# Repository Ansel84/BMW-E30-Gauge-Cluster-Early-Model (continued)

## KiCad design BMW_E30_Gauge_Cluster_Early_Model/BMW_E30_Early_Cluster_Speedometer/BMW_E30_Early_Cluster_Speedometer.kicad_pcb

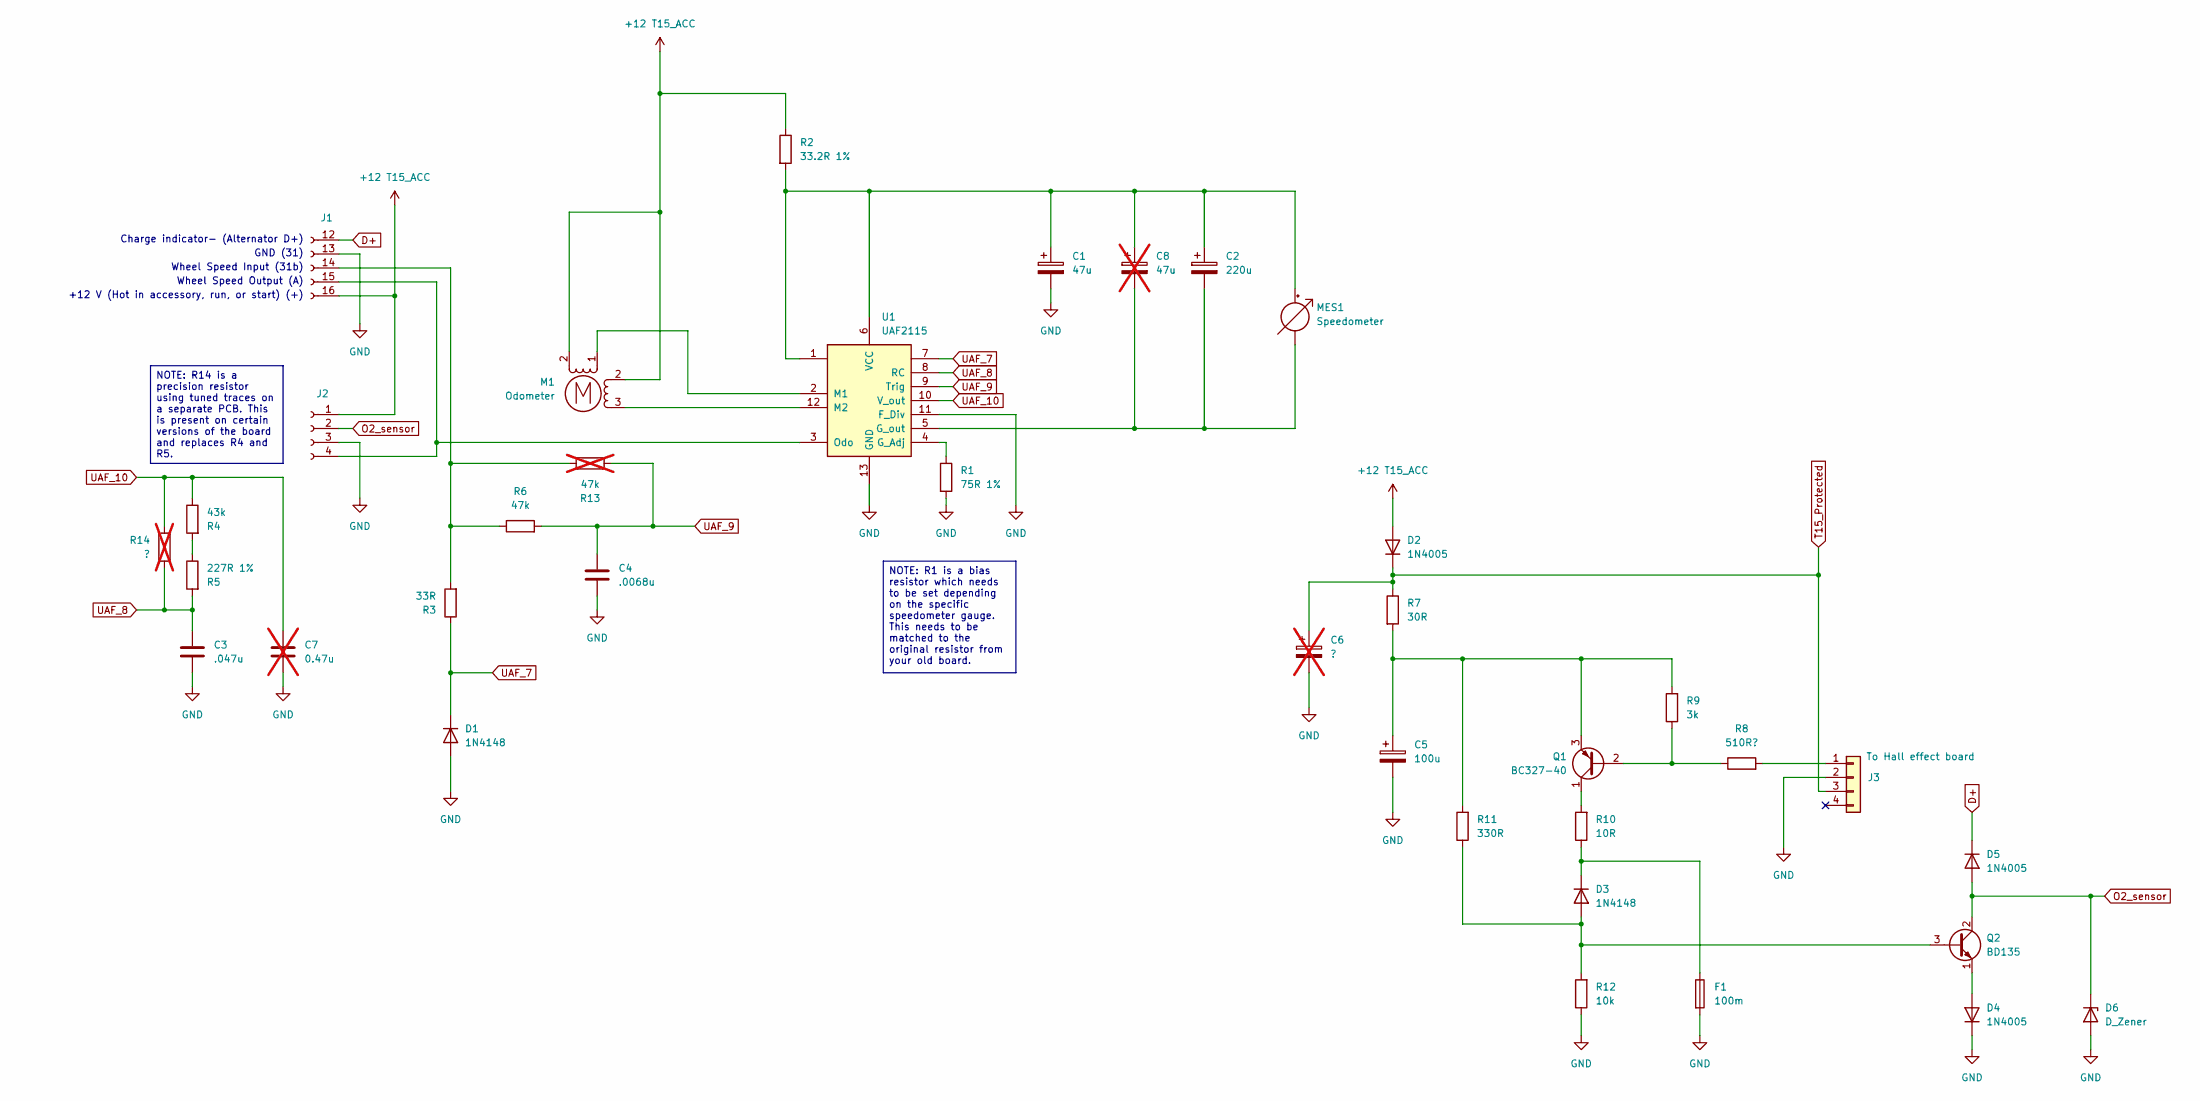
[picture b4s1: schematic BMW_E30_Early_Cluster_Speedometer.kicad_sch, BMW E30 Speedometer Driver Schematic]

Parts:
C1: 47u; CP_Radial_D6.3mm_P2.50mm
C2: 220u; CP_Radial_D10.0mm_P5.00mm
C3: .047u; C_Rect_L13.0mm_W4.0mm_P10.00mm_FKS3_FKP3_MKS4
C4: .0068u; C_Rect_L13.0mm_W4.0mm_P10.00mm_FKS3_FKP3_MKS4
C5: 100u; CP_Radial_D10.0mm_P5.00mm
C6: ?; CP_Radial_D10.0mm_P5.00mm; not fitted
C7: 0.47u; C_Disc_D7.5mm_W2.5mm_P5.00mm; not fitted
C8: 47u; CP_Radial_D6.3mm_P2.50mm; not fitted
D1, D3: 1N4148; D_DO-35_SOD27_P10.16mm_Horizontal
D2, D4, D5: 1N4005; D_DO-41_SOD81_P10.16mm_Horizontal
D6: D_Zener; D_DO-35_SOD27_P10.16mm_Horizontal
F1: 100m
J1: Conn_01x06_Socket; Connector_Speedometer
J2: Conn_01x04_Socket; BMW_1372218
J3: To Hall effect board; PinHeader_1x04_P2.54mm_Vertical
M1: Odometer; Odometer_Stepper
MES1: Speedometer; Speedometer_Galvanometer
Q1: BC327-40; TO-92_Inline
Q2: BD135; TO-126-3_Vertical
R1: 75R 1%; R_Axial_DIN0207_L6.3mm_D2.5mm_P10.16mm_Horizontal
R2: 33.2R 1%; R_Axial_DIN0207_L6.3mm_D2.5mm_P10.16mm_Horizontal
R3: 33R; R_Axial_DIN0207_L6.3mm_D2.5mm_P10.16mm_Horizontal
R4: 43k; R_Axial_DIN0207_L6.3mm_D2.5mm_P10.16mm_Horizontal
R5: 227R 1%; R_Axial_DIN0207_L6.3mm_D2.5mm_P10.16mm_Horizontal
R6: 47k; R_Axial_DIN0207_L6.3mm_D2.5mm_P10.16mm_Horizontal
R7: 30R; R_Axial_DIN0207_L6.3mm_D2.5mm_P10.16mm_Horizontal
R8: 510R?; R_Axial_DIN0207_L6.3mm_D2.5mm_P10.16mm_Horizontal
R9: 3k; R_Axial_DIN0207_L6.3mm_D2.5mm_P10.16mm_Horizontal
R10: 10R; R_Axial_DIN0207_L6.3mm_D2.5mm_P10.16mm_Horizontal
R11: 330R; R_Axial_DIN0207_L6.3mm_D2.5mm_P10.16mm_Horizontal
R12: 10k; R_Axial_DIN0207_L6.3mm_D2.5mm_P10.16mm_Horizontal
R13: 47k; R_Axial_DIN0207_L6.3mm_D2.5mm_P10.16mm_Horizontal; not fitted
R14: ?; R_Axial_DIN0207_L6.3mm_D2.5mm_P5.08mm_Vertical; not fitted
U1: UAF2115

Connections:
+12 T15_ACC: D2.2 (A), J1.16 (Pin_5), J2.1, M1.2, R2.1
D+: D5.1 (K), J1.12 (Pin_1)
GND: C1.2, C3.2, C4.2, C5.2, C6.2, C7.2, D1.2 (A), D4.1 (K), D6.2 (A), F1.2, J1.13 (Pin_2), J2.3, J3.2, R1.2, R12.1, U1.11 (F_Div), U1.13 (GND)
unnamed: D3.2 (A), Q2.3 (B), R11.1, R12.2
unnamed: D3.1 (K), F1.1, R10.1
unnamed: D4.2 (A), Q2.1 (E)
unnamed: J1.14 (Pin_3), R3.2, R6.1, R13.1
unnamed: J1.15 (Pin_4), J2.4, U1.3 (Odo)
unnamed: J3.1, R8.2
unnamed: C1.1, C2.1, C8.1, MES1.2 (+), R2.2, U1.1, U1.6 (VCC)
unnamed: C2.2, C8.2, MES1.1 (-), U1.5 (G_out)
unnamed: Q1.2 (B), R8.1, R9.1
unnamed: Q1.1 (C), R10.2
unnamed: C5.1, Q1.3 (E), R7.2, R9.2, R11.2
unnamed: R4.2, R5.1
unnamed: R1.1, U1.4 (G_Adj)
unnamed: M1.1, U1.2 (M1)
unnamed: M1.3, U1.12 (M2)
O2_sensor: D5.2 (A), D6.1 (K), J2.2, Q2.2 (C)
T15_Protected: C6.1, D2.1 (K), J3.3, R7.1
UAF_7: D1.1 (K), R3.1, U1.7
UAF_8: C3.1, R5.2, R14.1, U1.8 (RC)
UAF_9: C4.1, R6.2, R13.2, U1.9 (Trig)
UAF_10: C7.1, R4.1, R14.2, U1.10 (V_out)

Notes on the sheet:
+12 V (Hot in accessory, run, or start) (+)
GND (31)
Wheel Speed Output (A)
Charge indicator- (Alternator D+)
Wheel Speed Input (31b)
NOTE: R14 is a precision resistor using tuned traces on a separate PCB. This is present on certain versions of the board and replaces R4 and R5.
NOTE: R1 is a bias resistor which needs to be set depending on the specific speedometer gauge. This needs to be matched to the original resistor from your old board.

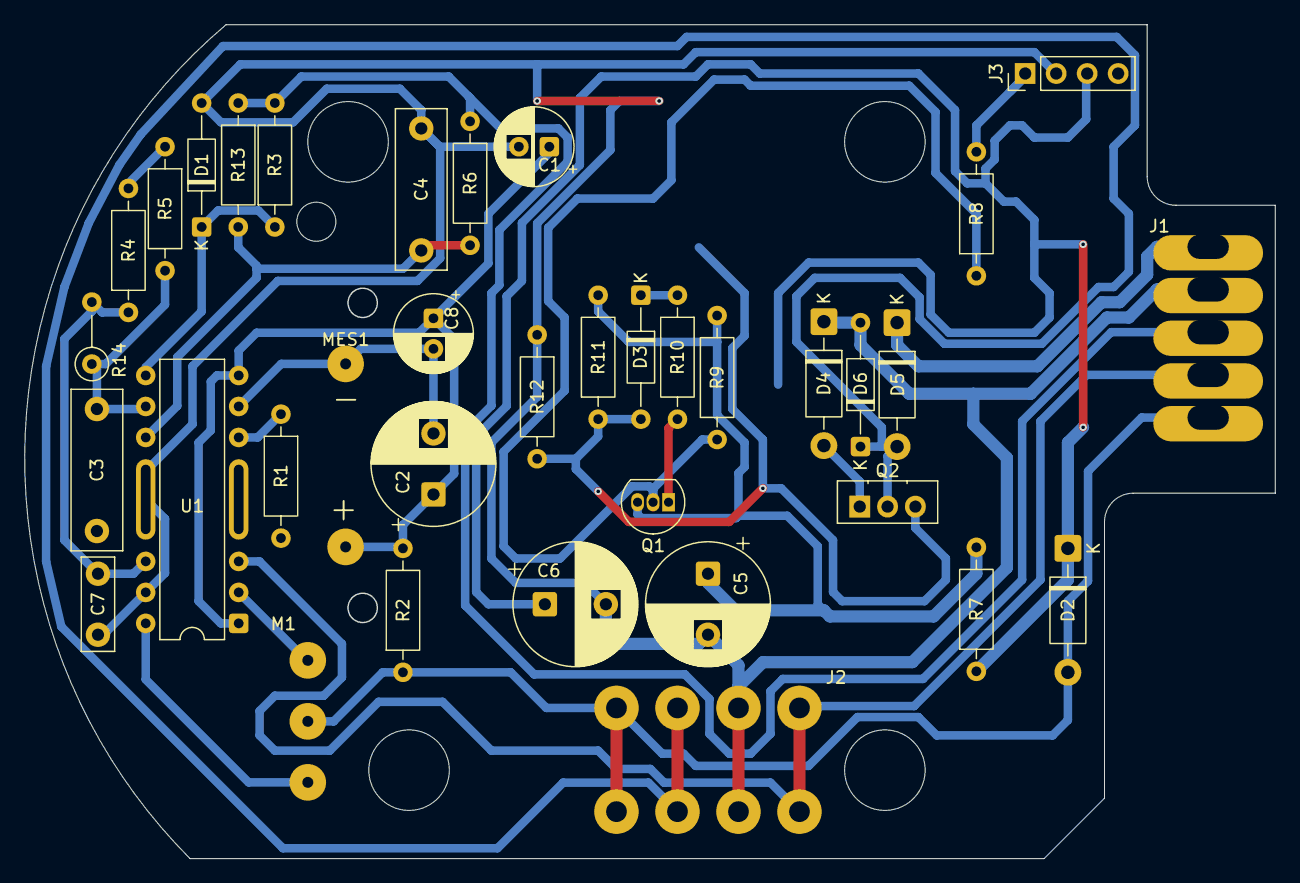
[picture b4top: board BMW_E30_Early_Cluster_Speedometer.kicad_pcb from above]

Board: 2 copper layers, 102.5 x 68.3 mm, 36 parts (0 on the bottom side), 24 nets.

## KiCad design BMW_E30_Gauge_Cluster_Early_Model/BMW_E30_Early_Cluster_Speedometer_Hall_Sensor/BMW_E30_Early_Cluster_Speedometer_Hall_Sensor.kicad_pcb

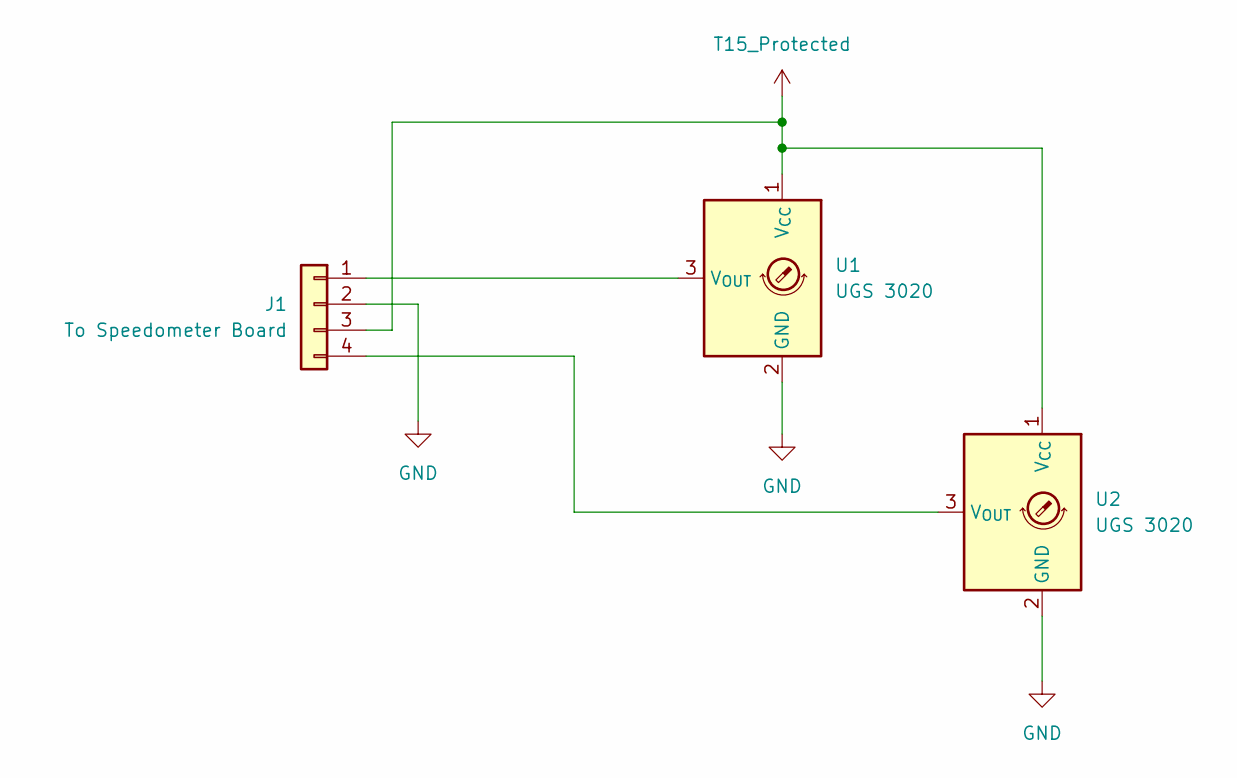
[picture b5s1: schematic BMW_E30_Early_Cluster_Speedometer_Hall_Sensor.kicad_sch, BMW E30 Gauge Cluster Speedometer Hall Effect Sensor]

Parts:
J1: To Speedometer Board; PinHeader_1x04_P2.54mm_Horizontal
U1, U2: UGS 3020; TO-92S

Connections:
GND: J1.2, U1.2 (GND), U2.2 (GND)
unnamed: J1.1, U1.3 (V_{OUT})
unnamed: J1.4, U2.3 (V_{OUT})
T15_Protected: J1.3, U1.1 (V_{CC}), U2.1 (V_{CC})

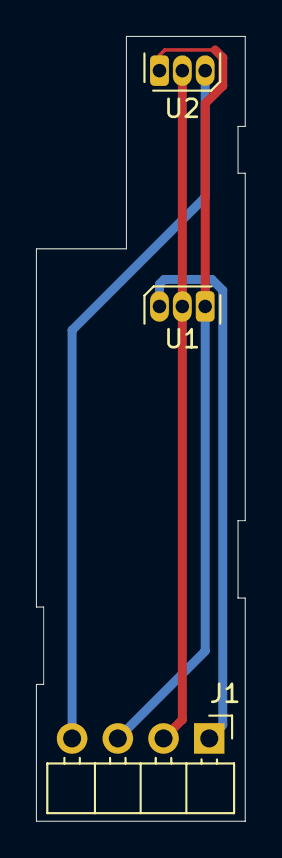
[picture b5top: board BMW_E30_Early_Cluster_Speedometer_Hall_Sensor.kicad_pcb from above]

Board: 2 copper layers, 11.6 x 43.6 mm, 3 parts (0 on the bottom side), 4 nets.

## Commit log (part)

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2025-08-19 Change Silkscreen
2025-08-20 Layout Updates
    Layout changes made after first laser cut board comparison.
2025-08-21 Update J3 Footprint Key
2025-08-25 Added Library for custom symbols
    Added the UAF2115 speedometer driver IC symbol
2025-08-26 Created Schematic for Speedometer Board
2025-08-26 Speedometer PCB Started
2025-08-26 Schematic Correction & Resources
    Corrected an error in the schematic and also added in a resources folder containing the datasheet for the SAF2115 chip on the board.
2025-08-27 Layout Updates
    Drew out board cut outlines and 2 clearance holes for the speedometer mounts. Added footprint for O2 sensor connector as well.
2025-08-28 Update Layout
    Updated layout footprint positions based on second laser cut prototype board.
2025-08-29 Schematic Updates
    Progress on full speedometer schematic
2025-08-29 Completed Schematic Diagram of Speedometer
    Make sure to verify schematic during layout with the reference board.
2025-08-29 Component Layout
    Rough layout of components completed
2025-08-30 Schematic & Layout Changes
    Made a few changes to the schematic, changing C2 and C8 connections. Locked in the galvanometer and odometer stepper footprint locations on the board.
2025-08-30 Layout Updates
    Added and located final mounting holes on the board.
2025-08-30 Added Hall Sensor Board
    Separate board was added for mounting the Hall effect sensor(s) to the main Speedometer board.
2025-08-30 Update Folder System
    Decided to make different kicad projects for each PCB, this includes the hall effect sensor board (previous commit), as well as the fuel economy gauge and tachometer gauge driver boards.
2025-08-31 Added Images for Tach and EG Boards
2025-08-31 Started Tach and EG Schematics
    Started pinouts for tachometer and EG schematics. Also made a notation update to the Nexus schematic, removed a TODO that was completed.
2025-09-01 Tachometer Schematic Completed
2025-09-01 Added Datasheets
    Datasheets for the chips on the EG board.
2025-09-01 EG Schematic Updates
2025-09-03 Updates to EG Schematic
2025-09-04 EG Schematic Completed
2025-09-04 Removed deprecated txt file
2025-09-12 Updates to Nexus Layout
2025-09-17 Board Cuts for EG
    started on board cuts for the economy gauge
2025-09-18 Layout Updates for EG
    TODO: fix reference designators that were rewritten by accident. Original reference designators are listed in the schematic pdf.
2025-09-23 EG Layout Updates
2025-10-13 Silkscreen Updates
2025-10-13 Layout fixes for first board order
2025-10-19 Add pdf schematic copies
2025-10-21 First Board Run Updates
    Changed locations of C1, a few mounting holes, and hole sizes on connector IV and connector V.
2025-10-22 Changes to Silkscreen and GBR Generation
    Modified silkscreen to be slightly larger font. Also generated GBR files for second board run with updated footprints and cut locations.
2025-10-26 Add Digikey Part Numbers
    Added digikey part numbers for resistors and connectors for ordering purposes.
2025-10-30 EG Layout Updates
    Added capacitor footprints and moved all resistors into place.
2025-10-31 Layout Updates
    Added footprints for coding plug, econometer gauge, and D5.
    Also fixed pin number 28 on U6.
2025-11-01 Layout Updates for EG
    Added footprints for J1 and J2 connectors. Also Changed footprint for RN1 to match original board. Next step is to route traces.
2025-11-01 Added IC Symbol
    Added symbol for SN29736P to the BMW IC's library and to the schematic.
2025-11-01 Component Placement on Tach Board
    Completed component placement part of layout for the tachometer pcb. All footprints are created and locations set. Final step is trace layout.
2025-11-01 Update README.md
    Updates to progress section.
2025-11-02 Added C1, C2, and C3 to footprint library
    consolodating symbols and footprints into the local library folder.
2025-11-03 Added Light Footprints to Library
2025-11-03 Updated Library Footprints in BMW connectors
2025-11-03 Update connector footprint library
2025-11-03 Fixing Library manager not seeing proper library files
2025-11-03 Connector Library Project Level Access
    Changed connector library to be project based instead of global.
2025-11-03 Fix Outdated Connector IV Hole Sizes
2025-11-03 Nexus Layout Updates + Footprint Updates
    Updated fuel gauge and temp gauge footprints to have their locating holes included. Also widened the mounting holes for both gauge footprints.
    Layout:
    Moved fuel gauge to the right by 1mm, moved blue connector down 1mm and left 0.5mm, moved white connector down 1mm.
2025-11-09 Standardized Board Location
    Made board location the same as the late model project to make component locations easy to map between both projects.
2025-11-10 Change Silkscreen on Nexus
    Changed "E30" to knockout text style to match style of late model board.
2025-11-10 Schematic Readability updates
    Changed connector naming to include part numbers for reference purposes. Updated date and version number on schematic, also exported new schematic v3 pdf.
2025-11-30 Add LICENSE file
2025-12-09 Move Board Cut Outline
    Moved board cut outlines up by 0.3mm to more closely match the original board's fit on the plastic back shell. Final step will be to update J5 to the new design from the late model project.
2026-01-12 Speedometer Board Layer update
    Changed the layer on which the reference image was placed from edge.cuts to user.1 so it can be hidden
2026-01-18 Updated Connector V Footprint
2026-01-19 Update Silkscreen for Connector V
2026-01-23 Added Note to Speedometer Schematic
2026-01-24 Tach Board Layout Complete
2026-01-25 Layout for EG started
2026-01-30 GBR files updated
2026-02-01 Layout Updates
2026-03-14 Update all Schematic pdfs
2026-06-04 Update Schematic PDFs
